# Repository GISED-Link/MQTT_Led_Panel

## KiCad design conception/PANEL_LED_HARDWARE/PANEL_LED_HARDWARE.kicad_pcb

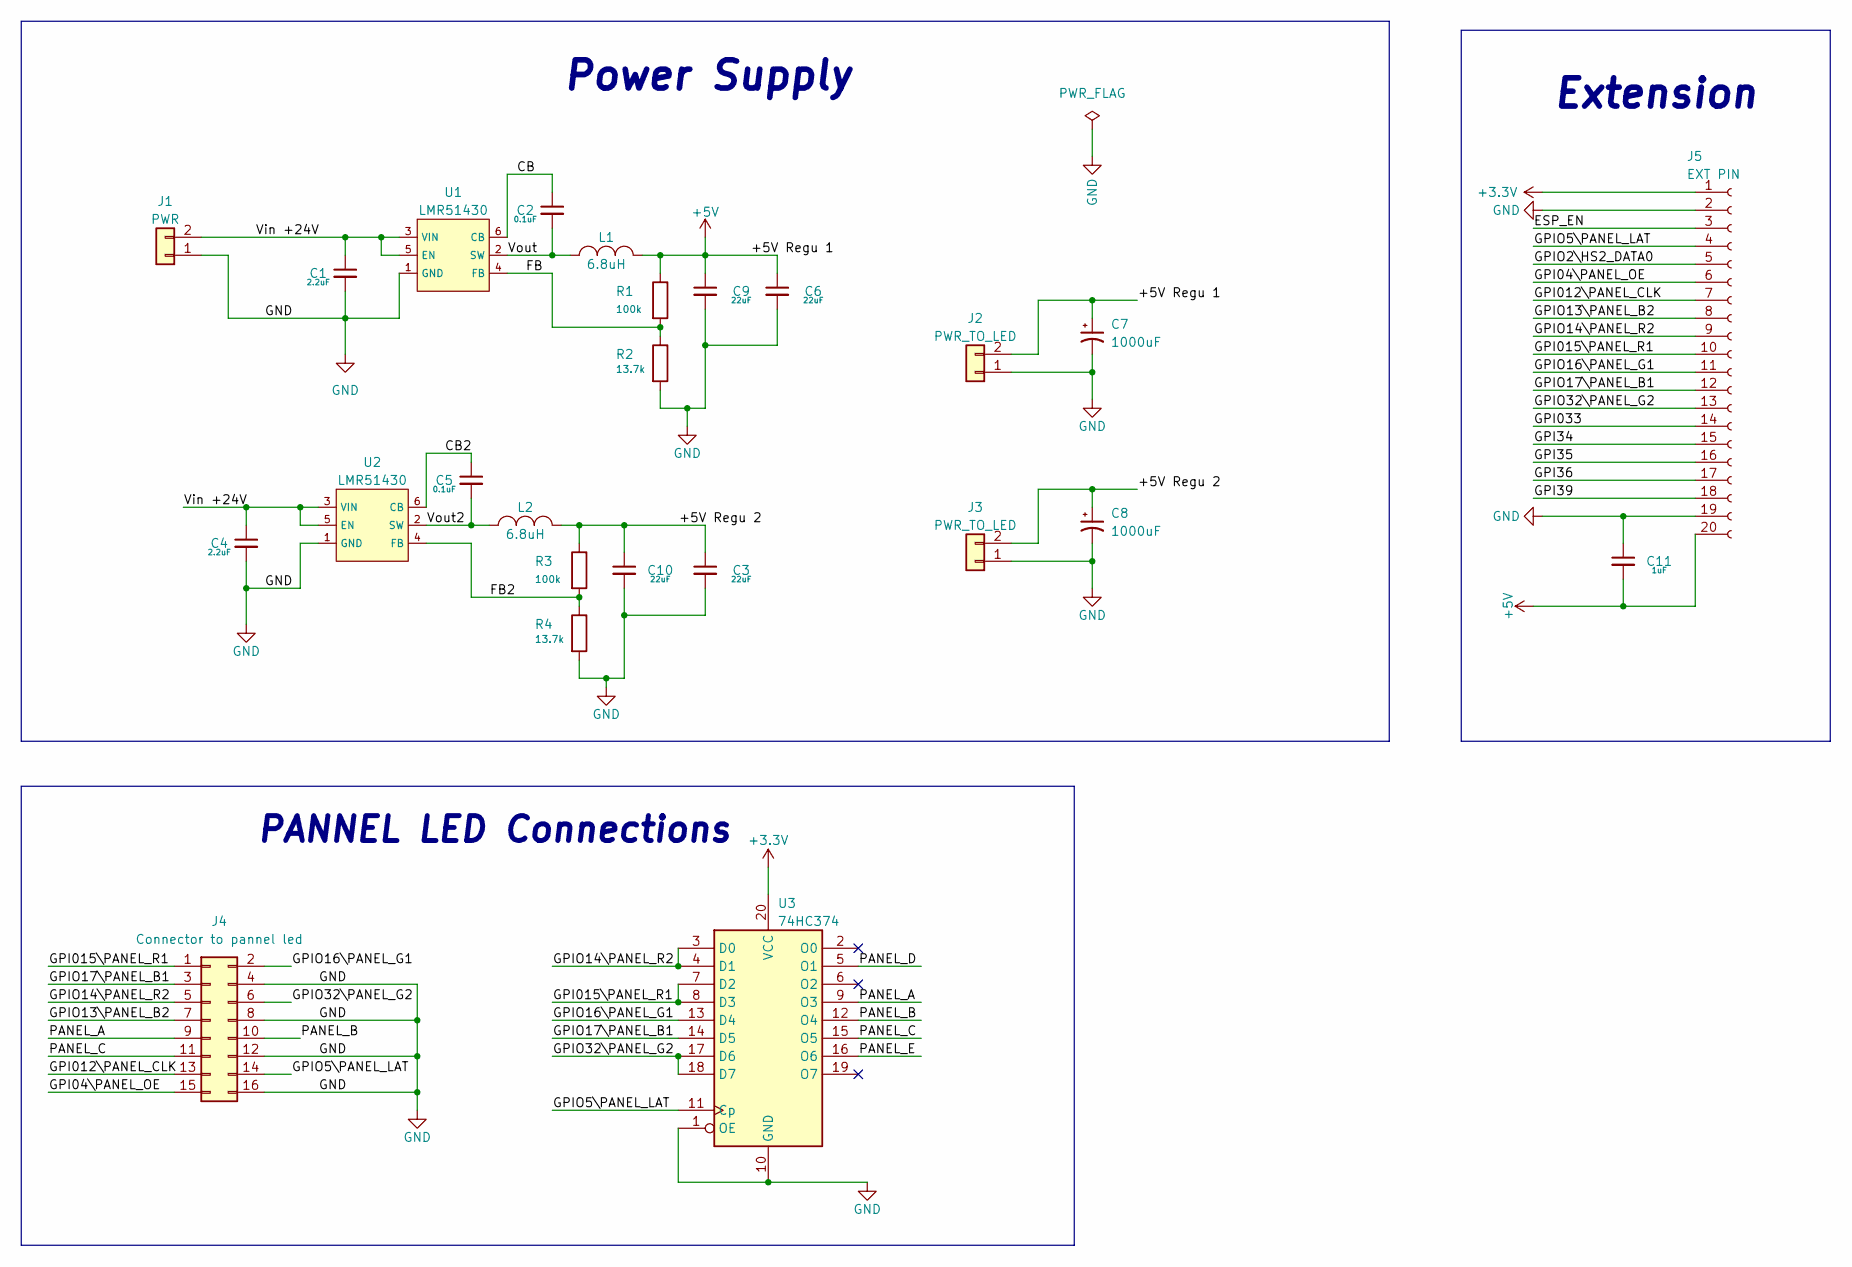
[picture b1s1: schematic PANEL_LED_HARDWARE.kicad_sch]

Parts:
C1, C4: 2.2uF; C_0603_1608Metric
C2, C5: 0.1uF; C_0603_1608Metric
C3, C6, C9, C10: 22uF; C_0603_1608Metric
C7, C8: 1000uF; Capa1000uF
C11: 1uF; C_0603_1608Metric
J1: PWR; BORNIER_2P
J2, J3: PWR_TO_LED; BORNIER_2P
J4: Connector to pannel led; PANEL_CONNECTOR
J5: EXT PIN; HN1x20
L1, L2: 6.8uH; L_Bourns_SRN6045TA
R1, R3: 100k; R_0201_0603Metric
R2, R4: 13.7k; R_0201_0603Metric
U1, U2: LMR51430
U3: 74HC374; SOIC-20

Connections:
+3V3: J5.1, U3.20 (VCC)
+5V: C6.1, C7.1, C9.1, C11.2, J2.2, J5.20, L1.2, R1.1
/+5V Regu 2: C3.1, C8.1, C10.1, J3.2, L2.2, R3.1
/CB: C2.1, U1.6 (CB)
/CB2: C5.1, U2.6 (CB)
/ESP_EN: J5.3
/FB: R1.2, R2.1, U1.4 (FB)
/FB2: R3.2, R4.1, U2.4 (FB)
/GPI04\PANEL_OE: J4.15, J5.6
/GPI012\PANEL_CLK: J4.13, J5.7
/GPI015\PANEL_R1: J4.1, J5.10, U3.7 (D2), U3.8 (D3)
/GPI033: J5.14
/GPI34: J5.15
/GPI35: J5.16
/GPI36: J5.17
/GPI39: J5.18
/GPIO2\HS2_DATA0: J5.5
/GPIO5\PANEL_LAT: J4.14, J5.4, U3.11 (Cp)
/GPIO13\PANEL_B2: J4.7, J5.8
/GPIO14\PANEL_R2: J4.5, J5.9, U3.3 (D0), U3.4 (D1)
/GPIO16\PANEL_G1: J4.2, J5.11, U3.13 (D4)
/GPIO17\PANEL_B1: J4.3, J5.12, U3.14 (D5)
/GPIO32\PANEL_G2: J4.6, J5.13, U3.17 (D6), U3.18 (D7)
/PANEL_A: J4.9, U3.9 (O3)
/PANEL_B: J4.10, U3.12 (O4)
/PANEL_C: J4.11, U3.15 (O5)
/PANEL_D: U3.5 (O1)
/PANEL_E: U3.16 (O6)
/Vin +24V: C1.1, C4.1, J1.2, U1.3 (VIN), U1.5 (EN), U2.3 (VIN), U2.5 (EN)
/Vout: C2.2, L1.1, U1.2 (SW)
/Vout2: C5.2, L2.1, U2.2 (SW)
GND: C1.2, C3.2, C4.2, C6.2, C7.2, C8.2, C9.2, C10.2, C11.1, J1.1, J2.1, J3.1, J4.4, J4.8, J4.12, J4.16, J5.2, J5.19, R2.2, R4.2, U1.1 (GND), U2.1 (GND), U3.1 (OE), U3.10 (GND)

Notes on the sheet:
Extension
PANNEL LED Connections
Power Supply

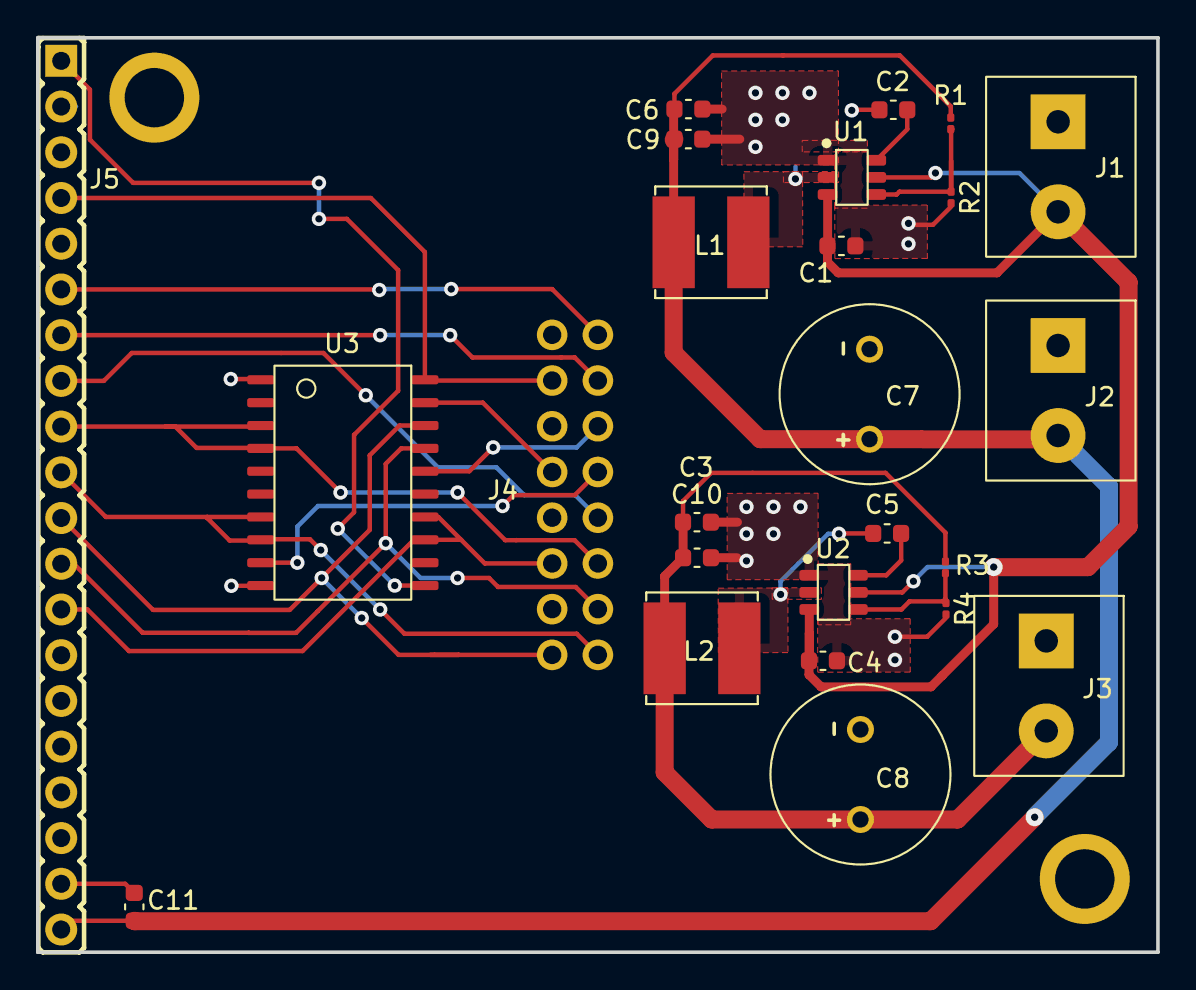
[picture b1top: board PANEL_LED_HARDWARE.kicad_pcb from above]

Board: 2 copper layers, 62.2 x 50.8 mm, 25 parts (1 on the bottom side), 23 nets.

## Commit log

2022-10-27 Update schematic
    New ref ( LMR51430 ) for the 24/5V converter
    Add package for alim and panel connecter
2022-11-01 Update hardware add latch
2022-11-01 Update hardware to connect daugther board
2022-11-01 Add open source hardware mother board
2022-11-03 Add modification to compile arduino libraries
2022-11-03 Add code from the other project MQTT keypad
2022-11-03 Update PCB and add footprints
2022-11-04 First version for routage
2022-11-07 Update PCB routage
    Increase pistes width for 24V 5V and GND
    Change power supply for buffer 5V=>3.3V
    Add GND and other signal plan like the example in the datasheet (LMR51430)
    Move connectors
2022-11-07 Solve problem on logo
2022-11-08 Review PCB
2022-11-08 Create REV A
2022-11-10 Script for MQTT com
2022-11-10 Change MQTT code to correspond to the new project
2022-11-10 Add code to send data to the panel
2022-11-10 Bug solve (task trigger watchdog)
2022-11-11 Add thread to spam the broker
2022-11-11 Bug solve
    The display task's watermark never decrease under 2072 words so I increase the stack value to 4096 word and in this case I received more than 8000 messages without stack overflow
2022-11-11 Clean code
2022-11-15 Format code + add configuration through uart
2022-11-17 test com buffer
2022-11-18 test buffer with change_line function
